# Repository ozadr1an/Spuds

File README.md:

Spuds
=====
**A Teensylu / Printrboard Mashup**

Spuds was born from mashing together the concepts of both the Teensylu and Printrboard (itself a development of the Teensylu concept). The aim was to take the positives provided by the Printrboard design and incorporate some additions such as LED indicators on the MOSFETs, an additional PWM Fan header and an extra PWM Output header pin. It then reintroduced the modular Stepper Driver setup, as for many, the onboard Allegro drivers of the Printrboard are seen as a drawback as it limits options and replacement/repair. 

Spuds has expansion headers supporting I2C, SPI, UART, and ADC pins. All extra I/O ports of the AT90USB have been broken out to headers for prototyping and expansion. It follows the footprint for headers that the Printrboard introduced to allow compatibility with other expansions devices such as LCD's and the Extrudr board. 

The continued use of the AT90USB1286 used in the Teensylu and Printrboard means Spuds also has on-chip USB, removing the need for the FTDI UART (USB-to-serial) IC. On-chip USB means dramatically faster firmware upload times and communication. The AT90USB connects at any baud rate regardless of firmware configuration, and operates virtually free of serial communication errors/pauses.

This board is currently in pre-release design phases, so is subject to changes!

**Licence: _CC ShareAlike 3.0_**

**Attributions:**
* **_Teensylu_** (StephS 2011) http://reprap.org/wiki/Teensylu
* **_Printrboard_** (Laine Walker-Avina 2012) http://reprap.org/wiki/Printrboard

##Features
* Small design - board is 100mm x 60mm (4" x 2.4")
* Atmel AT90USB1286 Microcontroller (or AT90USB1287 drop-in compatible for 20mhz support)
 * Native USB interface. No FTDI serial-to-USB chip.
 * 128kb Flash
* Modular Stepper Driver Support (Add/Replace as needed)
* Solder Jumper Microstepping Selection
* Thermistor Connectivity: 2
* N-MOSFETs for Extruder and Heatbed control
 * LED Status Indicators for Power, HBP and Extruder (Troubleshooting, PID Monitoring)
* 2 N-MOSFET for low power Fan or motor
* 6 2-Pin Header 12V Connections for additional features such as LEDs, Cooling Fans, etc
* Onboard SD card slot
* Four Endstop connectors 
 * User selectable via Solder Jumpers 5V or 12v Rails.
 * Includes X, Y, Z, and fourth endstop called E-Stop to be used as an emergency stop, or extruder stop (to be added in firmware).
* Supports multiple power configurations (Carried from Sanguinololu)
 * Logic & Motors supplied by ATX or laptop power supply (12-20V 120W minimum)
 * Logic supplied by USB bus (if enabled by solder jumper)
 * Logic supplied by on-board voltage regulator
 * On-board USB connectivity
* Edge connectors enabling use of vertical or right-angle connections
* 15 Extra pins available for expansion and development, with the following capabilities
 * UART1 (RX and TX)
 * I2C (SDA and SCL)
 * SPI (MOSI, MISO, SCK)
 * PWM pin (2)
 * Analog I/O (6)
 * JTAG (uses some of the ADC pins)
 * Additional 14 pin header with remaining I/O for prototyping
 * SMT Components sized at 0805, and no QFNs for easier soldering.
 * 2-Layer PCB to reduce manufacture cost & complexity

####Benefits of this Design
* Allows modular use of Stepper Drivers, allowing:
 * User selection of driver used
 * The re-use of existing drivers
 * Replacement due to fault/failure.

* Integrated USB controller provides 12MBps bandwidth, instead of usual slower serial comms via FTDI. Result: Virtually no serial communication errors and interruptions due to PC Activity reduced.
* Integrated micro-SD Card slot
* Uses small standard Molex connectors for motors, heater, and endstops.

####Bill of Materials
Available via [GoogleDocs](https://docs.google.com/spreadsheet/ccc?key=0ArIeeziM0bp9dG5TbjlYaFVDQ0I5dkZXbHk2VjhtQlE&usp=sharing)

####Revision History
* V0.5 [July 2013]: Internal pre-production design.

####Compatible Firmwares
* Sprinter: http://reprap.org/wiki/Sprinter
* Marlin: No official support yet, but works with Lincomatic's fork (https://github.com/lincomatic/Marlin) or the Unofficial Solidoodle Firmware (https://github.com/mlaws/solidoodle2-marlin)
* Repetier List_of_Firmware#Repetier-Firmware: Supported, use MOTHERBOARD == 8. (https://github.com/repetier/Repetier-Firmware)
* grbl: No official support yet, but works with Lincomatic's fork. (http://blog.lincomatic.com/?p=564)

(Other firmwares are currently untested but any firmware for an arduino mega should work with proper pin setup.)

####Alternate Bootloader
If you have an ISP or JTAG cable, you can also program an alternate bootloader from the LUFA project that allows you to potentially program with the standard Arduino software.
* Download BootloaderCDC.zip
* Unzip to get BootloaderCDC.hex
* Program using your favorite ISP/JTAG cable.
 * The command for avrdude is avrdude -p at90usb1286 -c <your programmer here> -U flash:w:BootloaderCDC.hex

###Setup
####Stepper Motors
Connect the X, Y, Z axis, and extruder motors to the matching headers at the top of the Printrboard (X-MOT, Y-MOT, Z-MOT, E-MOT). Headers are 4 wire Molex KK series, part# 0022013047) with 2759 series crimp terminals, part# 0008550101. Motor pinout is:
1. A - Phase 1+
2. B - Phase 1-
3. C - Phase 2+
4. D - Phase 2-

####Endstops
Connect mechanical microswitches to the 3-pin Molex headers X-STOP, Y-STOP, Z-STOP at the bottom of the board. E-STOP is reserved for future use. Connect switches as follows:
#####Standard Microswitches
1. Switch NC
2. No connection
3. Switch COMMON

#####For optos:
1. Signal Output
2. +5V or +12V
3. GND

####Heaters
* LEDs are fitted to indicate when the MOSFET is active. These can be ommitted if desired. 
* Connect the heating element of your hotend (resistor or nichrome wire) to the 4-pin EXTRUDER header, positioned next to MOSFET Q1. 
* Connect your heatbed to the HOTBED header, next to MOSFET Q2. Polarity here is unimportant; pinout is as follows:

1. Positive
2. Positive
3. Negative
4. Negative

####Thermistors
Thermistor headers are 2-pin Molex headers at the right side of the board, located above the reset button.
* Connect the HBP thermistor to the header directly above the reset button. 
* The Extruder thermistor also connects above the reset button next to the HBP thermistor.

####Low Power Fan
A 2-pin Molex header labelled FAN is located on the right side of the board, above the thermistor headers. 
* This optional header can be used to power a fan or other small motor.

####Board Power
All power is supplied through a choice of connector at the upper left corner of the Spuds, labelled PWR:
* 4-pin ATX style header (Suitable for high current HBP)
* 5.08mm 2-Pin Screw Terminal (Suitable for low current HBP only)

Connect directly to any 12VDC power supply. 
* Ground terminals are closest to the edge of the board
* 12VDC+ terminals are located behind.

####USB
Choice of USB Connector (only one can be installed). The Type-B connector is a good choice for long cable runs, as you can easily acquire heavily sheilded thick gauge USB cables as used for Printers. Micro-USB is perhaps a good choice if a small compact connection is required, or for interconnection to another controller system such as a tablet or RPi:
* Micro-USB B Connector
* Type-B USB Connector

**Note that a jumper should _NOT_ be installed on the "BOOT" pins for normal operation (see _Bootloaders_ ).**

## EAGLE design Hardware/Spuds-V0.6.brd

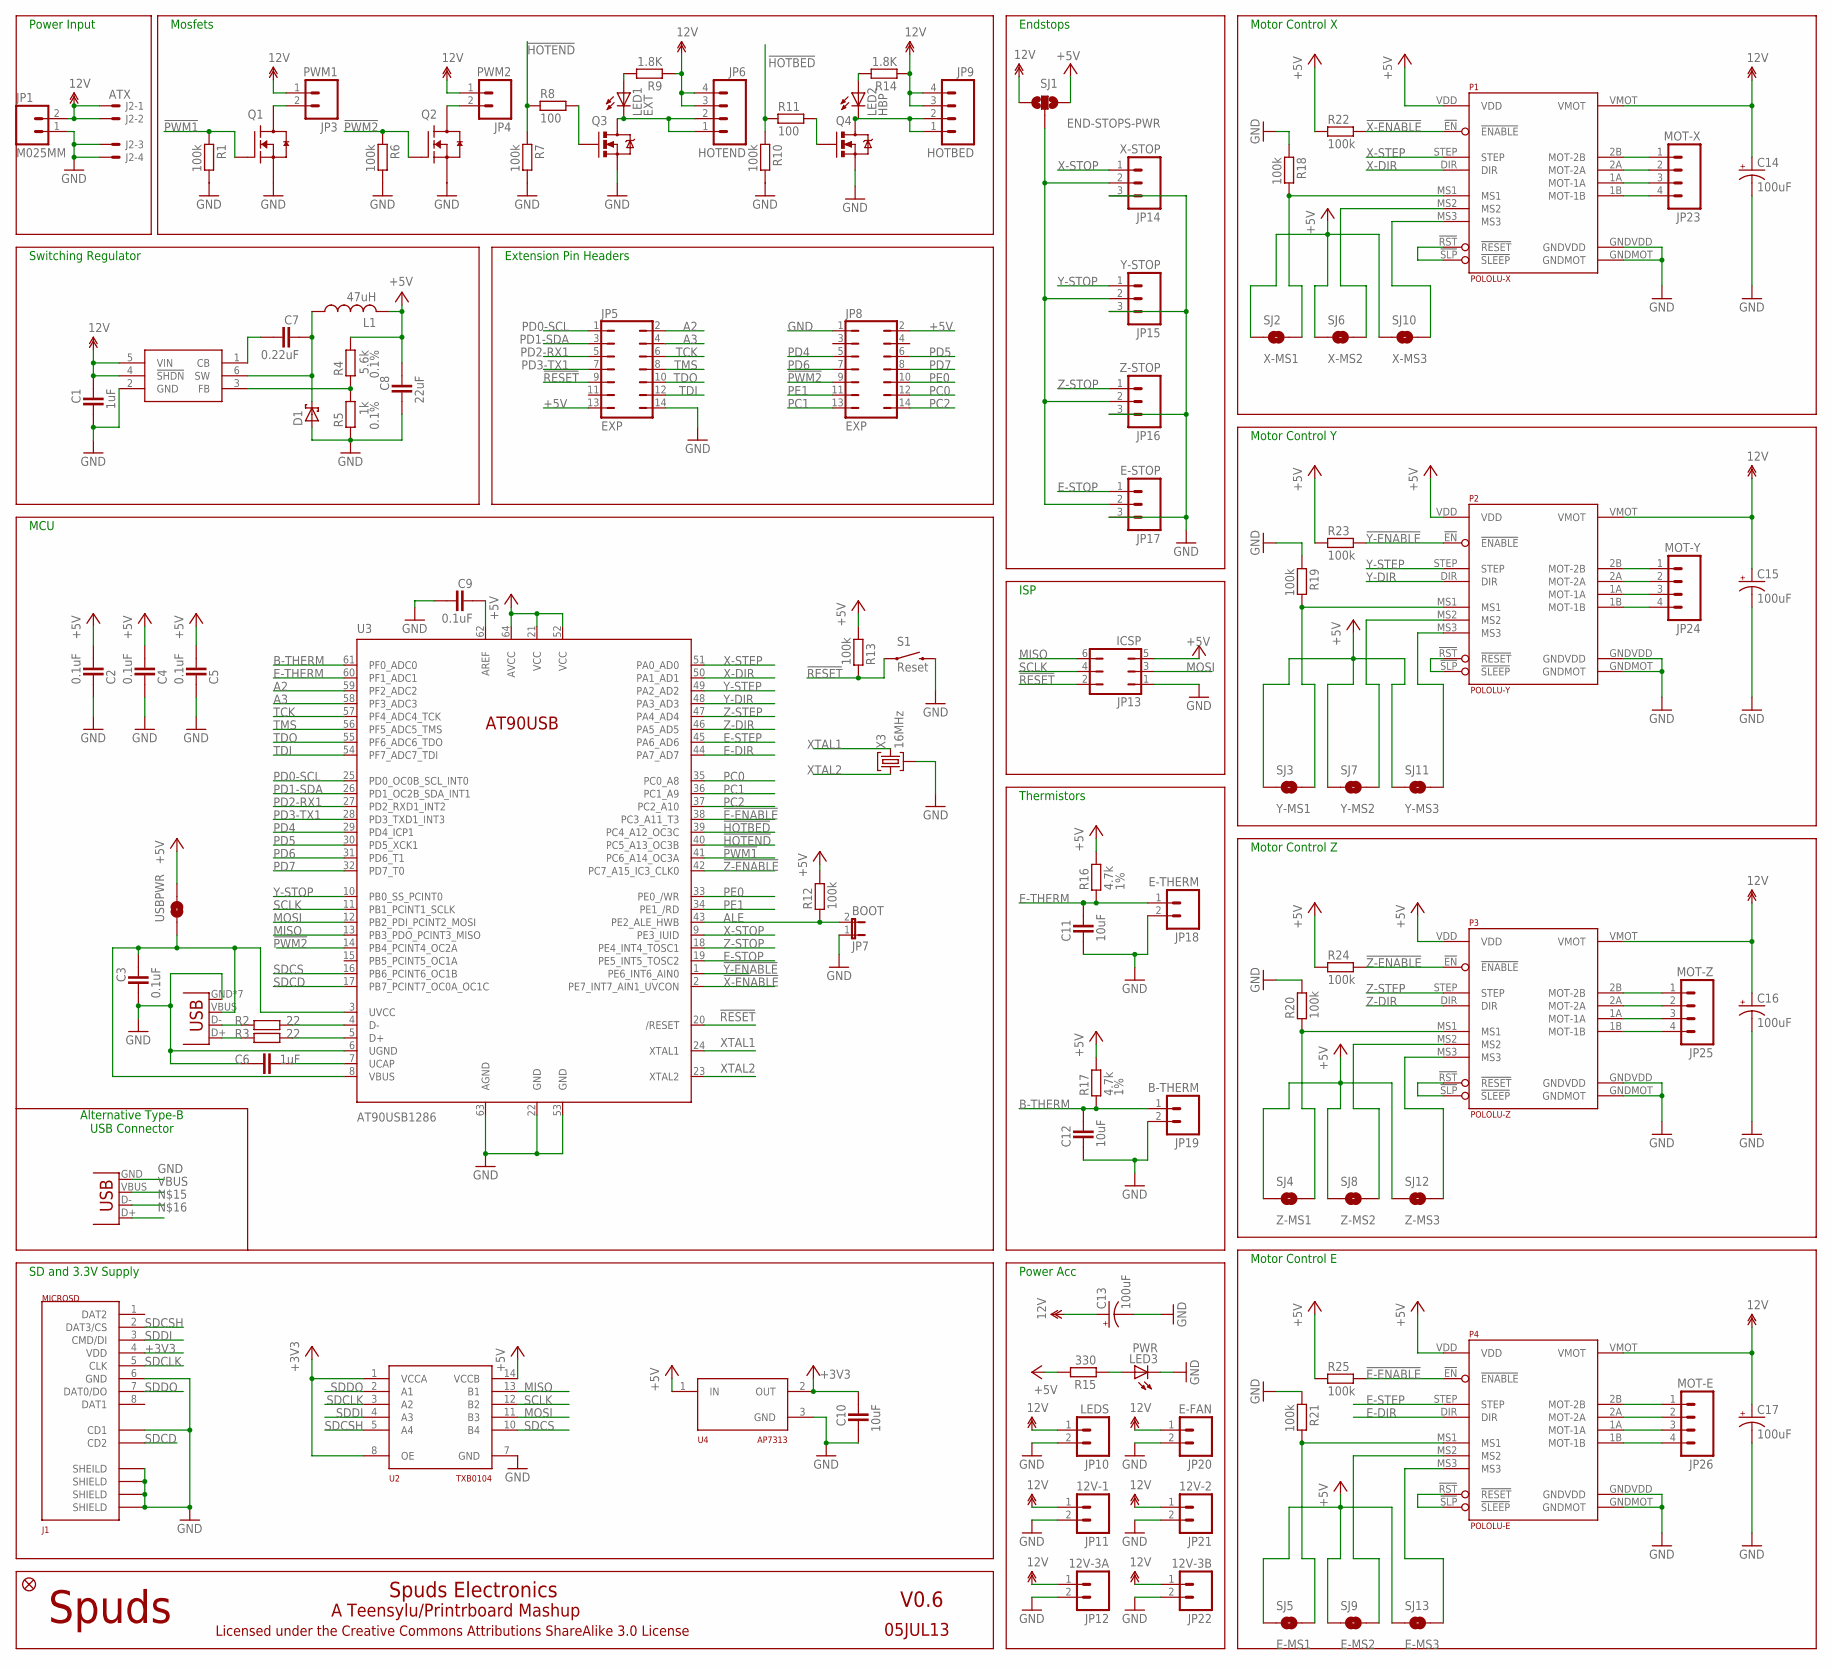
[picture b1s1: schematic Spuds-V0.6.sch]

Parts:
C1, C6: 1uF; CAPC2012X145AN; PARTNO 587-2229-1-ND
C2, C3, C4, C5, C9: 0.1uF; CAPC2012X145AN; PARTNO 311-1361-1-ND
C7: 0.22uF; CAPC2012X145AN; PARTNO 399-3491-1-ND
C8: 22uF; CAPC2012X145AN; PARTNO 587-1305-1-ND
C10, C11, C12: 10uF; CAPC2012X145AN; PARTNO 311-1355-1-ND
C13, C14, C15, C16, C17: 100uF; PANASONIC_D; PARTNO PCE3951CT-ND
D1: SCH-DIODESMA; SMA; PARTNO B140-FDICT-ND
J1: MICROSD; AMPHENOL-MICROSD; PARTNO ED2983-ND
J2: ATX; 5566-4; PARTNO WM3801-ND
JP1: M025MM; SCREWTERMINAL-5MM-2; PARTNO A98355-ND
JP2: FIDUCIAL1X2.5; FIDUCIAL-1X2.5; PARTNO *
JP3: PWM1; 1X02; PARTNO WM4000-ND
JP4: PWM2; 1X02; PARTNO WM4000-ND
JP5, JP8: EXP; JP7Q; PARTNO 609-3491-ND
JP6: HOTEND; MOLEX-1X4; PARTNO WM4113-ND
JP7: BOOT; 1X02; PARTNO WM4000-ND
JP9: HOTBED; MOLEX-1X4; PARTNO WM4113-ND
JP10: LEDS; 1X02; PARTNO WM4000-ND
JP11: 12V-1; 1X02; PARTNO WM4111-ND
JP12: 12V-3A; 1X02; PARTNO WM4111-ND
JP13: ICSP; JP3Q; PARTNO 609-3210-ND
JP14: X-STOP; MOLEX-1X3; PARTNO WM4112-ND
JP15: Y-STOP; MOLEX-1X3; PARTNO WM4112-ND
JP16: Z-STOP; MOLEX-1X3; PARTNO WM4112-ND
JP17: E-STOP; MOLEX-1X3; PARTNO WM4112-ND
JP18: E-THERM; 1X02; PARTNO WM4111-ND
JP19: B-THERM; 1X02; PARTNO WM4111-ND
JP20: E-FAN; 1X02; PARTNO WM4111-ND
JP21: 12V-2; 1X02; PARTNO WM4111-ND
JP22: 12V-3B; 1X02; PARTNO WM4111-ND
JP23: MOT-X; MOLEX-1X4; PARTNO WM4113-ND
JP24: MOT-Y; MOLEX-1X4; PARTNO WM4113-ND
JP25: MOT-Z; MOLEX-1X4; PARTNO WM4113-ND
JP26: MOT-E; MOLEX-1X4; PARTNO WM4113-ND
L1: 47uH; SDR1006; PARTNO SDR1006-470KLCT-ND
LED1: EXT; CHIP-LED0805; PARTNO 754-1132-1-ND
LED2: HBP; CHIP-LED0805; PARTNO 754-1437-1-ND
LED3: PWR; CHIP-LED0805; PARTNO 754-1131-1-ND
P1: POLOLU-X; POLOLU-ALLEGRO-PTH; PARTNO 952-1823-ND
P2: POLOLU-Y; POLOLU-ALLEGRO-PTH; PARTNO 952-1823-ND
P3: POLOLU-Z; POLOLU-ALLEGRO-PTH; PARTNO 952-1823-ND
P4: POLOLU-E; POLOLU-ALLEGRO-PTH; PARTNO 952-1823-ND
Q1, Q2: RFP30N06LE; SOT95P280X135-3N; PARTNO IRLML2060TRPBFCT-ND
Q3, Q4: RFP30N06LE; TO220V; PARTNO IRLB8743PBF-ND
R1, R6, R7, R10, R12, R13, R18, R19, R20, R21, R22, R23, R24, R25: 100k; RESC2012X70N; PARTNO RMCF0805JT100KCT-ND
R2, R3: 22; RESC2012X70N; PARTNO 311-22ARCT-ND
R4: 5.6k; RESC2012X70N; TOLERANCE 0.1%; PARTNO P5.6KDATR-ND
R5: 1k; RESC2012X70N; TOLERANCE 0.1%; PARTNO RG20P1.0KBCT-ND
R8, R11: 100; RESC2012X70N; PARTNO 311-100ARCT-ND
R9, R14: 1.8K; RESC2012X70N; PARTNO 311-1.8LHCT-ND
R15: 330; RESC2012X70N; PARTNO 311-330ARCT-ND
R16, R17: 4.7k; RESC2012X70N; TOLERANCE 1%; PARTNO 311-4.70KCRCT-ND
S1: Reset; TACTILE_SWITCH_TALL; PARTNO 450-1133-ND
SJ1: END-STOPS-PWR; SJ_3_PASTE2&3; PARTNO *
SJ2: X-MS1; SJ_2S; PARTNO *
SJ3: Y-MS1; SJ_2S; PARTNO *
SJ4: Z-MS1; SJ_2S; PARTNO *
SJ5: E-MS1; SJ_2S; PARTNO *
SJ6: X-MS2; SJ_2S; PARTNO *
SJ7: Y-MS2; SJ_2S; PARTNO *
SJ8: Z-MS2; SJ_2S; PARTNO *
SJ9: E-MS2; SJ_2S; PARTNO *
SJ10: X-MS3; SJ_2S; PARTNO *
SJ11: Y-MS3; SJ_2S; PARTNO *
SJ12: Z-MS3; SJ_2S; PARTNO *
SJ13: E-MS3; SJ_2S; PARTNO *
U1: LM2841; TSOT6; PARTNO LM2841XMK-ADJLCT-ND
U2: TXB0104; TSSOP14; PARTNO 296-21929-1-ND
U3: AT90USB1286; TQFP64-2; PARTNO AT90USB1286-AURCT-ND
U4: AP7313; SOT23C; PARTNO AP7313-33SAG-7DICT-ND
USBPWR: SOLDERJUMPERNO; SJ_2S-NO; PARTNO *
X1: USBPTH; USB-B-PTH; PARTNO ED2983-ND
X2: USB-MICROB; PARTNO 455-2562-1-ND
X3: 16MHz; AWSCR; PARTNO 535-10011-1-ND

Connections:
12V: C1.1, C13.+, C14.+, C15.+, C16.+, C17.+, J2.1, J2.2, JP1.2, JP3.1, JP4.1, JP6.3, JP6.4, JP9.3, JP9.4, JP10.1, JP11.1, JP12.1, JP20.1, JP21.1, JP22.1, P1.VMOT, P2.VMOT, P3.VMOT, P4.VMOT, R9.1, R14.1, SJ1.1, U1.4 (!SHDN), U1.5 (VIN)
!E-ENABLE: P4.!EN (!ENABLE), R25.2, U3.38 (PC3_A11_T3)
!HOTBED: R10.1, R11.1, U3.39 (PC4_A12_OC3C)
!HOTEND: R7.1, R8.1, U3.40 (PC5_A13_OC3B)
!PWM1: Q1.1 (G), R1.1, U3.41 (PC6_A14_OC3A)
!PWM2: JP8.9, Q2.1 (G), R6.1, U3.14 (PB4_PCINT4_OC2A)
!RESET: JP5.9, JP13.2, R13.1, S1.A2 (1), U3.20 (/RESET)
!X-ENABLE: P1.!EN (!ENABLE), R22.2, U3.2 (PE7_INT7_AIN1_UVCON)
!Y-ENABLE: P2.!EN (!ENABLE), R23.2, U3.1 (PE6_INT6_AIN0)
!Z-ENABLE: P3.!EN (!ENABLE), R24.2, U3.42 (PC7_A15_IC3_CLK0)
+3V3: C10.1, J1.4 (VDD), U2.1 (VCCA), U2.8 (OE), U4.2 (OUT)
+5V: C2.2, C4.2, C5.2, C8.1, JP5.13, JP8.2, JP13.5, L1.P$2 (2), P1.VDD, P2.VDD, P3.VDD, P4.VDD, R4.1, R12.2, R13.2, R15.2, R16.2, R17.2, R22.1, R23.1, R24.1, R25.1, SJ1.3, SJ2.1, SJ3.1, SJ4.1, SJ5.1, SJ6.1, SJ7.1, SJ8.1, SJ9.1, SJ10.1, SJ11.1, SJ12.1, SJ13.1, U2.14 (VCCB), U3.21 (VCC), U3.52 (VCC), U3.64 (AVCC), U4.1 (IN), USBPWR.2
A2: JP5.2, U3.59 (PF2_ADC2)
A3: JP5.4, U3.58 (PF3_ADC3)
ALE: JP7.2, R12.1, U3.43 (PE2_ALE_HWB)
AREF: C9.1, U3.62 (AREF)
B-THERM: C12.2, JP19.1, R17.1, U3.61 (PF0_ADC0)
E-DIR: P4.DIR, U3.44 (PA7_AD7)
E-MS1: P4.MS1, R21.2, SJ5.2
E-MS2: P4.MS2, SJ9.2
E-MS3: P4.MS3, SJ13.2
E-RESETSLEEP: P4.!RST (!RESET), P4.!SLP (!SLEEP)
E-STEP: P4.STEP, U3.45 (PA6_AD6)
E-STOP: JP17.1, U3.19 (PE5_INT5_TOSC2)
E-THERM: C11.2, JP18.1, R16.1, U3.60 (PF1_ADC1)
END-STOP-PWR: JP14.2, JP15.2, JP16.2, JP17.2, SJ1.2
GND: C1.2, C2.1, C3.2, C4.1, C5.1, C6.1, C8.2, C9.2, C10.2, C11.1, C12.1, C13.-, C14.-, C15.-, C16.-, C17.-, D1.A, J1.6 (GND), J1.C1 (SHEILD), J1.C2 (SHIELD), J1.C3 (SHIELD), J1.C4 (SHIELD), J1.CD1, J2.3, J2.4, JP1.1, JP5.14, JP7.1, JP8.1, JP10.2, JP11.2, JP12.2, JP13.1, JP14.3, JP15.3, JP16.3, JP17.3, JP18.2, JP19.2, JP20.2, JP21.2, JP22.2, LED3.C, P1.GNDMOT, P1.GNDVDD, P2.GNDMOT, P2.GNDVDD, P3.GNDMOT, P3.GNDVDD, P4.GNDMOT, P4.GNDVDD, Q1.2 (S), Q2.2 (S), Q3.3 (S), Q4.3 (S), R1.2, R5.2, R6.2, R7.2, R10.2, R18.1, R19.1, R20.2, R21.1, S1.B2 (2), U1.2 (GND), U2.7 (GND), U3.6 (UGND), U3.22 (GND), U3.53 (GND), U3.63 (AGND), U4.3 (GND), X1.GND, X2.GND, X2.MT1 (GND), X2.MT2 (GND), X2.MT3 (GND), X2.MT4 (GND), X2.MT5 (GND), X2.MT6 (GND), X3.GND (2)
HOTBED-GND: JP9.1, JP9.2, LED2.C, Q4.2 (D)
HOTEND-GND: JP6.1, JP6.2, LED1.C, Q3.2 (D)
MISO: JP13.6, U2.13 (B1), U3.13 (PB3_PDO_PCINT3_MISO)
MOSI: JP13.3, U2.11 (B3), U3.12 (PB2_PDI_PCINT2_MOSI)
unnamed: LED3.A, R15.1
unnamed: LED1.A, R9.2
unnamed: R2.2, U3.4 (D-)
unnamed: R3.2, U3.5 (D+)
unnamed: LED2.A, R14.2
unnamed: JP3.2, Q1.3 (D)
unnamed: Q4.1 (G), R11.2
unnamed: JP24.2, P2.2A (MOT-2A)
unnamed: C6.2, U3.7 (UCAP)
unnamed: JP23.1, P1.2B (MOT-2B)
unnamed: JP23.2, P1.2A (MOT-2A)
unnamed: JP23.3, P1.1A (MOT-1A)
unnamed: JP23.4, P1.1B (MOT-1B)
unnamed: JP4.2, Q2.3 (D)
unnamed: R2.1, X1.D-, X2.D-
unnamed: R3.1, X1.D+, X2.D+
unnamed: R4.2, R5.1, U1.3 (FB)
unnamed: JP24.3, P2.1A (MOT-1A)
unnamed: JP24.4, P2.1B (MOT-1B)
unnamed: JP24.1, P2.2B (MOT-2B)
unnamed: JP26.1, P4.2B (MOT-2B)
unnamed: JP26.2, P4.2A (MOT-2A)
unnamed: JP26.3, P4.1A (MOT-1A)
unnamed: JP26.4, P4.1B (MOT-1B)
unnamed: Q3.1 (G), R8.2
unnamed: C7.1, D1.C, L1.P$1 (1), U1.6 (SW)
unnamed: C7.2, U1.1 (CB)
PC0: JP8.12, U3.35 (PC0_A8)
PC1: JP8.13, U3.36 (PC1_A9)
PC2: JP8.14, U3.37 (PC2_A10)
PD0-SCL: JP5.1, U3.25 (PD0_OC0B_SCL_INT0)
PD1-SDA: JP5.3, U3.26 (PD1_OC2B_SDA_INT1)
PD2-RX1: JP5.5, U3.27 (PD2_RXD1_INT2)
PD3-TX1: JP5.7, U3.28 (PD3_TXD1_INT3)
PD4: JP8.5, U3.29 (PD4_ICP1)
PD5: JP8.6, U3.30 (PD5_XCK1)
PD6: JP8.7, U3.31 (PD6_T1)
PD7: JP8.8, U3.32 (PD7_T0)
PE0: JP8.10, U3.33 (PE0_/WR)
PE1: JP8.11, U3.34 (PE1_/RD)
SCLK: JP13.4, U2.12 (B2), U3.11 (PB1_PCINT1_SCLK)
SDCD: J1.CD2, U3.17 (PB7_PCINT7_OC0A_OC1C)
SDCLK: J1.5 (CLK), U2.3 (A2)
SDCS: U2.10 (B4), U3.16 (PB6_PCINT6_OC1B)
SDCSH: J1.2 (DAT3/CS), U2.5 (A4)
SDDI: J1.3 (CMD/DI), U2.4 (A3)
SDDO: J1.7 (DAT0/DO), U2.2 (A1)
TCK: JP5.6, U3.57 (PF4_ADC4_TCK)
TDI: JP5.12, U3.54 (PF7_ADC7_TDI)
TDO: JP5.10, U3.55 (PF6_ADC6_TDO)
TMS: JP5.8, U3.56 (PF5_ADC5_TMS)
VBUS: C3.1, U3.3 (UVCC), U3.8 (VBUS), USBPWR.1, X1.VBUS, X2.VBUS
X-DIR: P1.DIR, U3.50 (PA1_AD1)
X-MS1: P1.MS1, R18.2, SJ2.2
X-MS2: P1.MS2, SJ6.2
X-MS3: P1.MS3, SJ10.2
X-RESETSLEEP: P1.!RST (!RESET), P1.!SLP (!SLEEP)
X-STEP: P1.STEP, U3.51 (PA0_AD0)
X-STOP: JP14.1, U3.9 (PE3_IUID)
XTAL1: U3.24 (XTAL1), X3.IN (3)
XTAL2: U3.23 (XTAL2), X3.OUT (1)
Y-DIR: P2.DIR, U3.48 (PA3_AD3)
Y-MS1: P2.MS1, R19.2, SJ3.2
Y-MS2: P2.MS2, SJ7.2
Y-MS3: P2.MS3, SJ11.2
Y-RESETSLEEP: P2.!RST (!RESET), P2.!SLP (!SLEEP)
Y-STEP: P2.STEP, U3.49 (PA2_AD2)
Y-STOP: JP15.1, U3.10 (PB0_SS_PCINT0)
Z-DIR: P3.DIR, U3.46 (PA5_AD5)
Z-MOT-1A: JP25.3, P3.1A (MOT-1A)
Z-MOT-1B: JP25.4, P3.1B (MOT-1B)
Z-MOT-2A: JP25.2, P3.2A (MOT-2A)
Z-MOT-2B: JP25.1, P3.2B (MOT-2B)
Z-MS1: P3.MS1, R20.1, SJ4.2
Z-MS2: P3.MS2, SJ8.2
Z-MS3: P3.MS3, SJ12.2
Z-RESETSLEEP: P3.!RST (!RESET), P3.!SLP (!SLEEP)
Z-STEP: P3.STEP, U3.47 (PA4_AD4)
Z-STOP: JP16.1, U3.18 (PE4_INT4_TOSC1)

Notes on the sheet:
Motor Control X
Motor Control Y
Motor Control Z
Motor Control E
ISP
Thermistors
Endstops
Mosfets
Power Acc
Spuds
V0.6
Spuds Electronics
Licensed under the Creative Commons Attributions ShareAlike 3.0 License
Extension Pin Headers
Switching Regulator
A Teensylu/Printrboard Mashup
SD and 3.3V Supply
Power Input
MCU
Alternative Type-B USB Connector
05JUL13

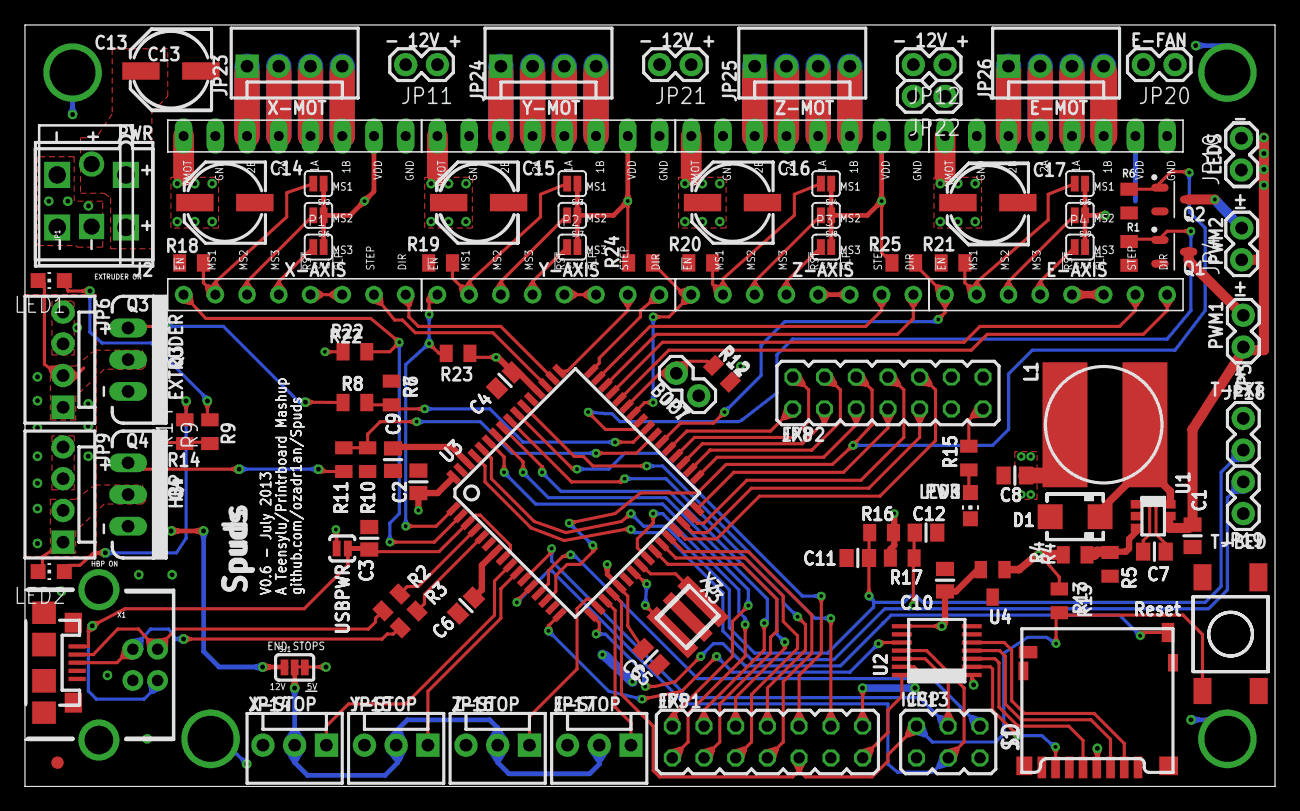
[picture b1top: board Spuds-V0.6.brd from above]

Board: 4 copper layers, 100.1 x 61.0 mm, 106 parts (0 on the bottom side), 110 nets.

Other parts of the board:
DRILEGEND: DRILEGEND

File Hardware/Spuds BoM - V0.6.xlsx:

Qty | Value | Device | Board Ref. | Digikey p/n | Unit Price | Total Part Price
1 | TXB0104 | TXB0104 Bi-Di Level Translator | U2 | 296-21929-1-ND | 0.743 | 0.743
1 | AP7313 | AP7313 3.3V LDO SOT-23 | U4 | AP7313-33SAG-7DICT-ND | 0.112 | 0.112
1 | AT90USB1286-AU | AT90USB | U3 | AT90USB1286-AURCT-ND | 6.14 | 6.14
1 | LM2841 | LM2841 Switching Regulator | U1 | LM2841XMK-ADJLCT-ND | 1.596 | 1.596
1 | BOOT | 0.1” 2-PIN MALE HEADER | JP7 | WM4000-ND | 0.063 | 0.063
2 | EXP | 0.1” 2X7 MALE PIN HEADER | JP5, JP8 | 609-3491-ND | 0.14166 | 0.28332
1 | ICSP | 0.1” 2X3 MALE PIN HEADER | JP13 | 609-3210-ND | 0.29275 | 0.29275
7 | LEDS/12V | 0.1” 2-PIN MALE HEADER | JP3, JP4, JP11, JP21, JP12, JP22, JP20 | WM4000-ND | 0.063 | 0.441
6 | MOTOR | 4-PIN 0.1” POLARIZED MOLEX KK-SERIES | JP6, JP9, JP23, JP24, JP25, JP26 | WM4113-ND | 0.17596 | 1.05576
2 | THERM | 2-PIN 0.1” POLARIZED MOLEX KK-SERIES | JP18, JP19 | WM4111-ND | 0.09237 | 0.18474
4 | ENDSTOP | 3-PIN 0.1” POLARIZED MOLEX KK-SERIES | JP14, JP15, JP16, JP17 | WM4112-ND | 0.13541 | 0.54164
2 | POLOLU-SOCKET | CONN HEADER 32POS SOCKET 2.54MM |  | 732-2860-ND | 1.34 | 2.68
1 | MICROSD | MICROSD Socket, Amphenol | J1 | 114-00841-68-1-ND | 0.856 | 0.856
1 | USB-PTH-B | CONN USB TYPE B R/A BLACK | X2 | ED2983-ND | 0.54 | 0.54
0 | USB-MICROB | USB-MICROB | X1 | 455-2562-1-ND | 0.5355 | 0
0 | PWR | TERM BLOCK 2POS SIDE ENTRY 5MM | JP1 | A98355-ND | 0.87 | 0
1 | ATX | Molex Mini-Fit Jr. 5566-4 | J3 | WM3801-ND | 0.33582 | 0.33582
1 | 20MHz | RESONATOR W/ INTEGRATED CAP | X3 | 535-10011-1-ND | 0.45 | 0.45
0 | 16MHz | RESONATOR W/ INTEGRATED CAP | X3 | 535-10008-2-ND | 0.182 | 0
5 | 0.1uF | CAPACITOR CERAMIC 0805 | C2, C3, C4, C5, C9 | 311-1361-1-ND | 0.006 | 0.03
1 | 0.22uF | CAPACITOR CERAMIC 0805 | C7 | 399-3491-1-ND | 0.02043 | 0.02043
2 | 1uF | CAPACITOR CERAMIC 0805 | C1, C6 | 587-2229-1-ND | 0.03055 | 0.0611
3 | 10uF | CAPACITOR CERAMIC 0805 | C10, C11, C12 | 311-1355-1-ND | 0.025 | 0.075
1 | 22uF | CAPACITOR CERAMIC 0805 | C8 | 587-1305-1-ND | 0.056 | 0.056
5 | 100uF | CAP, Al Electrolytic, Panasonic-D Pkg | C13, C14, C15, C16, C17 | PCE3951CT-ND | 0.1202 | 0.601
1 |  | DIODE SCHOTTKY 40V 1A SMA | D1 | B140-FDICT-ND | 0.0648 | 0.0648
1 | 47uH | Inductor, SMT 1.25A | L1 | SDR1006-470KLCT-ND | 0.3 | 0.3
3 | PWR | LED GREEN 0805 | LED1, LED2, LED3 | 754-1131-1-ND | 0.039 | 0.117
2 |  | Logic-level n-Chan MOSFET SOT-23 | Q1, Q2 | IRLML2060TRPBFCT-ND | 0.087 | 0.174
2 |  | Logic-level n-Chan MOSFET TO-220 | Q3, Q4 | IRLB8743PBF-ND | 0.52632 | 1.05264
1 | 1k | RESISTOR_0805 0.1% | R5 | RG20P1.0KBCT-ND | 0.058 | 0.058
2 | 1.8k | RESISTOR_0805 | R9, R14 | 311-1.8LHCT-ND | 0.058 | 0.116
2 | 4.7k | RESISTOR_0805 1% | R16, R17 | 311-4.70KCRCT-ND | 0.00266 | 0.00532
1 | 5.6k | RESISTOR_0805 0.1% | R4 | P5.6KDATR-ND | 0.013 | 0.013
2 | 22 | RESISTOR_0805 | R2, R3 | 311-22ARCT-ND | 0.00209 | 0.00418
2 | 100 | RESISTOR_0805 | R8, R11 | 311-100ARCT-ND | 0.00209 | 0.00418
14 | 100k | RESISTOR_0805 | R1, R6, R7, R10, R12, R13, R18, R19, R20, R21, R22, R23, R24, R25 | RMCF0805JT100KCT-ND | 0.0019 | 0.0266
1 | 330 | RESISTOR_0805 | R15 | 311-330ARCT-ND | 0.00209 | 0.00209
1 | Reset | SWITCH-MOMENTARY-2 | S2 | 450-1133-ND | 0.1398 | 0.1398
 |  |  |  |  | Total: | 19.23617

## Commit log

2013-07-07 Initial Schematic/Board Commit V0.6 BoM
2013-07-07 Images for v0.6 Added
2013-07-07 Update README.md
    Added Board/Schematic Images

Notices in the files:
parts and their libraries:
SparkFun-Passives: Licensing: CC v3.0 Share-Alike You are welcome to use this library for commercial purposes.
